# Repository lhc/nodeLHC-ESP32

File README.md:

## nodeLHC

# nodeLHC-ESP32

LIVE em formato Hands On Construindo o nova versão da placa de desenvolvimento nodeLHC ESP32, com o Pedro Minatel, utilizando a ferramenta Kicad, o módulo escolhido foi o ESP32 um microcontrolador de baixo custo da Espressif.

Em 2015 durante as oficinas de IoT no Hackerspace, criamos uma primeira versão do nodeLHC com o módulo ESP8266. Assim as pessoas aprenderam as diferentes etapas para construção de placa de circuitos impressos, também soldagem dos componentes da placa de desenvolvimento e programação para o módulo.

Descrições e detalhes:
Essa é uma primeira atividade que ao decorrer iremos construir novos projetos no formato aberto e colaborativo aproveitando a placa de desenvolvimento nodeLHC ESP32

- [KiCad](https://kicad.org/)
- [LHC KiCad Library](https://github.com/lhc/lhc_kicad_library)
- [Minatel KiCad Library](https://github.com/pedrominatel/minatel-kicad-libraries)
- [SparkFun KiCad Library](https://github.com/sparkfun/SparkFun-KiCad-Libraries)

# Checklist
- [x] LIVE 1 - Explicação geral e desenho
- [x] LIVE 2 - Revisão esquemático e desenho da PCB parcial
- [x] Lista de pessoas interessadas nos módulos
- [x] [20/11 às 20 horas : Feedback comunidade](https://discourse.lhc.net.br/t/parte-03-20-11-2020-coleta-de-feedback-do-nodelhc-esp32/225)
- [x] [LIVE 3 no dia 22 de janeiro de 2021 - Finalizar placa com KiCad](https://discourse.lhc.net.br/t/parte-05-finalizando-o-nodelhc-esp32-com-kicad/244)
- [x] Enviado o e-mail de confirmação aos interessados ao módulos ESP32
- [x] [Lista de interessados na compra coletiva](https://docs.google.com/forms/d/11yyAbOFoUoV5jsIAHc90laWFHk0OwfYHXRMlwPwyAws/edit)
- [x] Reunião online para novos revisores.
- [x] Validar artes na PCB (LHC/ Open Hardware)
- [x] [Videoconferência Revisão do nodeLHC: 25 Maio 2021 às 20 horas](meet.google.com/ngs-ypnc-mkd)

# Próximos passos
- [x] Convite Latinoware 2021
- [ ] Listar BOM / Orçamentos
- [ ] Produção da PCB
- [ ] LIVE de soldando o nodeLHC
- [ ] Distribuição para os participantes

# Checklist Review 01 nodeLHC

| Itens           | Check | Double Check  |
|---------------------|----------|----------|
| Alimentação 3V3| [Fechado](https://github.com/lhc/nodeLHC-ESP32/issues/2) | [Fechado](https://github.com/lhc/nodeLHC-ESP32/issues/9) |
| RX/TX| [Fechado](https://github.com/lhc/nodeLHC-ESP32/issues/3) | [Fechado](https://github.com/lhc/nodeLHC-ESP32/issues/10) |
| Reset e Boot| [Fechado](https://github.com/lhc/nodeLHC-ESP32/issues/4) | [Fechado](https://github.com/lhc/nodeLHC-ESP32/issues/11) |
| Conversor USB para UART| [Fechado](https://github.com/lhc/nodeLHC-ESP32/issues/5) | [Fechado](https://github.com/lhc/nodeLHC-ESP32/issues/12) |
| Conector Debug/JTAG| [Fechado](https://github.com/lhc/nodeLHC-ESP32/issues/6) | [Fechado](https://github.com/lhc/nodeLHC-ESP32/issues/13) |
| OLED| [Fechado](https://github.com/lhc/nodeLHC-ESP32/issues/7) | [Fechado](https://github.com/lhc/nodeLHC-ESP32/issues/14) |
| ESP32-WROMM pinout| [Fechado](https://github.com/lhc/nodeLHC-ESP32/issues/8) | [Fechado](https://github.com/lhc/nodeLHC-ESP32/issues/15) |

# Revisores
- Daniel
- Adrian
- Manassés
- Douglas

## Bill of Materials
| Component           | Quantity | Link                                             |
|---------------------|----------|--------------------------------------------------|
| ESP32-WROOM-   | 1        |                                                  |
|  |      |                                                  |

[Clique aqui](https://htmlpreview.github.io/?https://github.com/lhc/nodeLHC-ESP32/blob/master/projeto/bom/ibom.html) para ver a BOM interativa

Para gerar a BOM interativa, é necessário [instalar o plugin no KiCad](https://github.com/openscopeproject/InteractiveHtmlBom/wiki/Installation) e seguir as [orientações de uso](https://github.com/openscopeproject/InteractiveHtmlBom/wiki/Usage)

Para utilizar o plugin, no KiCad 6.x, após instalação concluída, utilize `PCB Editor > Tools > External Plugins > Generate Integractive HTML BOM`

# Vídeos gravados
- [Construindo o nodeLHC ESP32 com Kicad - Parte 01 #nodeLHC](https://youtu.be/l77AwA57H2A?t=1641)
- [Construindo o nodeLHC ESP32 com Kicad - Parte 02 #nodelhc](https://www.youtube.com/watch?v=WE6jsmoJX9M)
- [Construindo o nodeLHC ESP32 com Kicad - Parte 05](https://www.youtube.com/watch?v=1r1fcpELneA)

# Discourse
Dúvidas? sugestões publicar na issues ou direto no discourse do LHC
- [Parte 01 - 28/07/2020 LIVE - Hands On: Construindo o nodeLHC ESP32 com Kicad](https://discourse.lhc.net.br/t/28-07-2020-live-hands-on-construindo-o-nodelhc-esp32-com-kicad/148/2)
- [Parte 02 - Hands On: Construindo o nodeLHC ESP32 com Kicad](https://discourse.lhc.net.br/t/11-09-2020-live-hands-on-construindo-o-nodelhc-esp32-com-kicad-parte-02/160)
- [Parte 03 - Feedback comunidade](https://discourse.lhc.net.br/t/parte-03-20-11-2020-coleta-de-feedback-do-nodelhc-esp32/225)
- [Parte 04 - Melhorias para o nodeLHC ESP32](https://discourse.lhc.net.br/t/parte-04-melhorias-para-o-nodelhc-esp32/230/2)
- [Parte 05 - 22/01 às 20 horas: Hands On: Construindo o nodeLHC ESP32 com Kicad](https://discourse.lhc.net.br/t/parte-05-finalizando-o-nodelhc-esp32-com-kicad/244)

# Documentações em outras plataformas
- [Hackday.io](https://hackaday.io/project/177704-lhc-tijolo32-esp32-development-board)

# Log
- 19/08/2020 - Criado o evento, repositório, publicações nas redes sociais gerado link sobre a atividade.
- 02/09/2020 - Criado, divulgado o segundo evento, atualização de links no repositório.
- 06/10/2020 - Listagem das pessoas que responderam o discourse para receber o módulo ESP32
- 07/10/2020 - Chegaram os módulos.
- 17/11/2020 - Agendada conversa de feedback do projeto, divulgação da atividade.
- 16/01/2021 - Pedro fez update conforme o último encontro de feedback.
- 17/01/2021 - Atualizado no repositório, criado agenda de LIVE para o dia 22 de janeiro de 2021.
- 07/02/2021 - Enviado e-mail aos interessados aos módulos
             - Divulgação da compra coletiva de componentes para o nodeLHC
- 11/03/2021 - Atualização de revisão e update no projeto
- 16/03/2021 - Atualização de imagens e links de gravações
- 30/05/2021 - Feedback do Daniel registrado e atualização no README.md

### Referências
- [ESP32 Datasheet](https://www.espressif.com/sites/default/files/documentation/esp32_datasheet_en.pdf)
- [ESP32-WROOM Datasheet](https://www.espressif.com/sites/default/files/documentation/esp32-wroom-32d_esp32-wroom-32u_datasheet_en.pdf)
- [ESP32 Design Guidelines](https://www.espressif.com/sites/default/files/documentation/esp32_hardware_design_guidelines_en.pdf)
- [CH340G](https://cdn.sparkfun.com/datasheets/Dev/Arduino/Other/CH340DS1.PDF)
- [Open Source Hardware Association](https://www.oshwa.org/definition/)

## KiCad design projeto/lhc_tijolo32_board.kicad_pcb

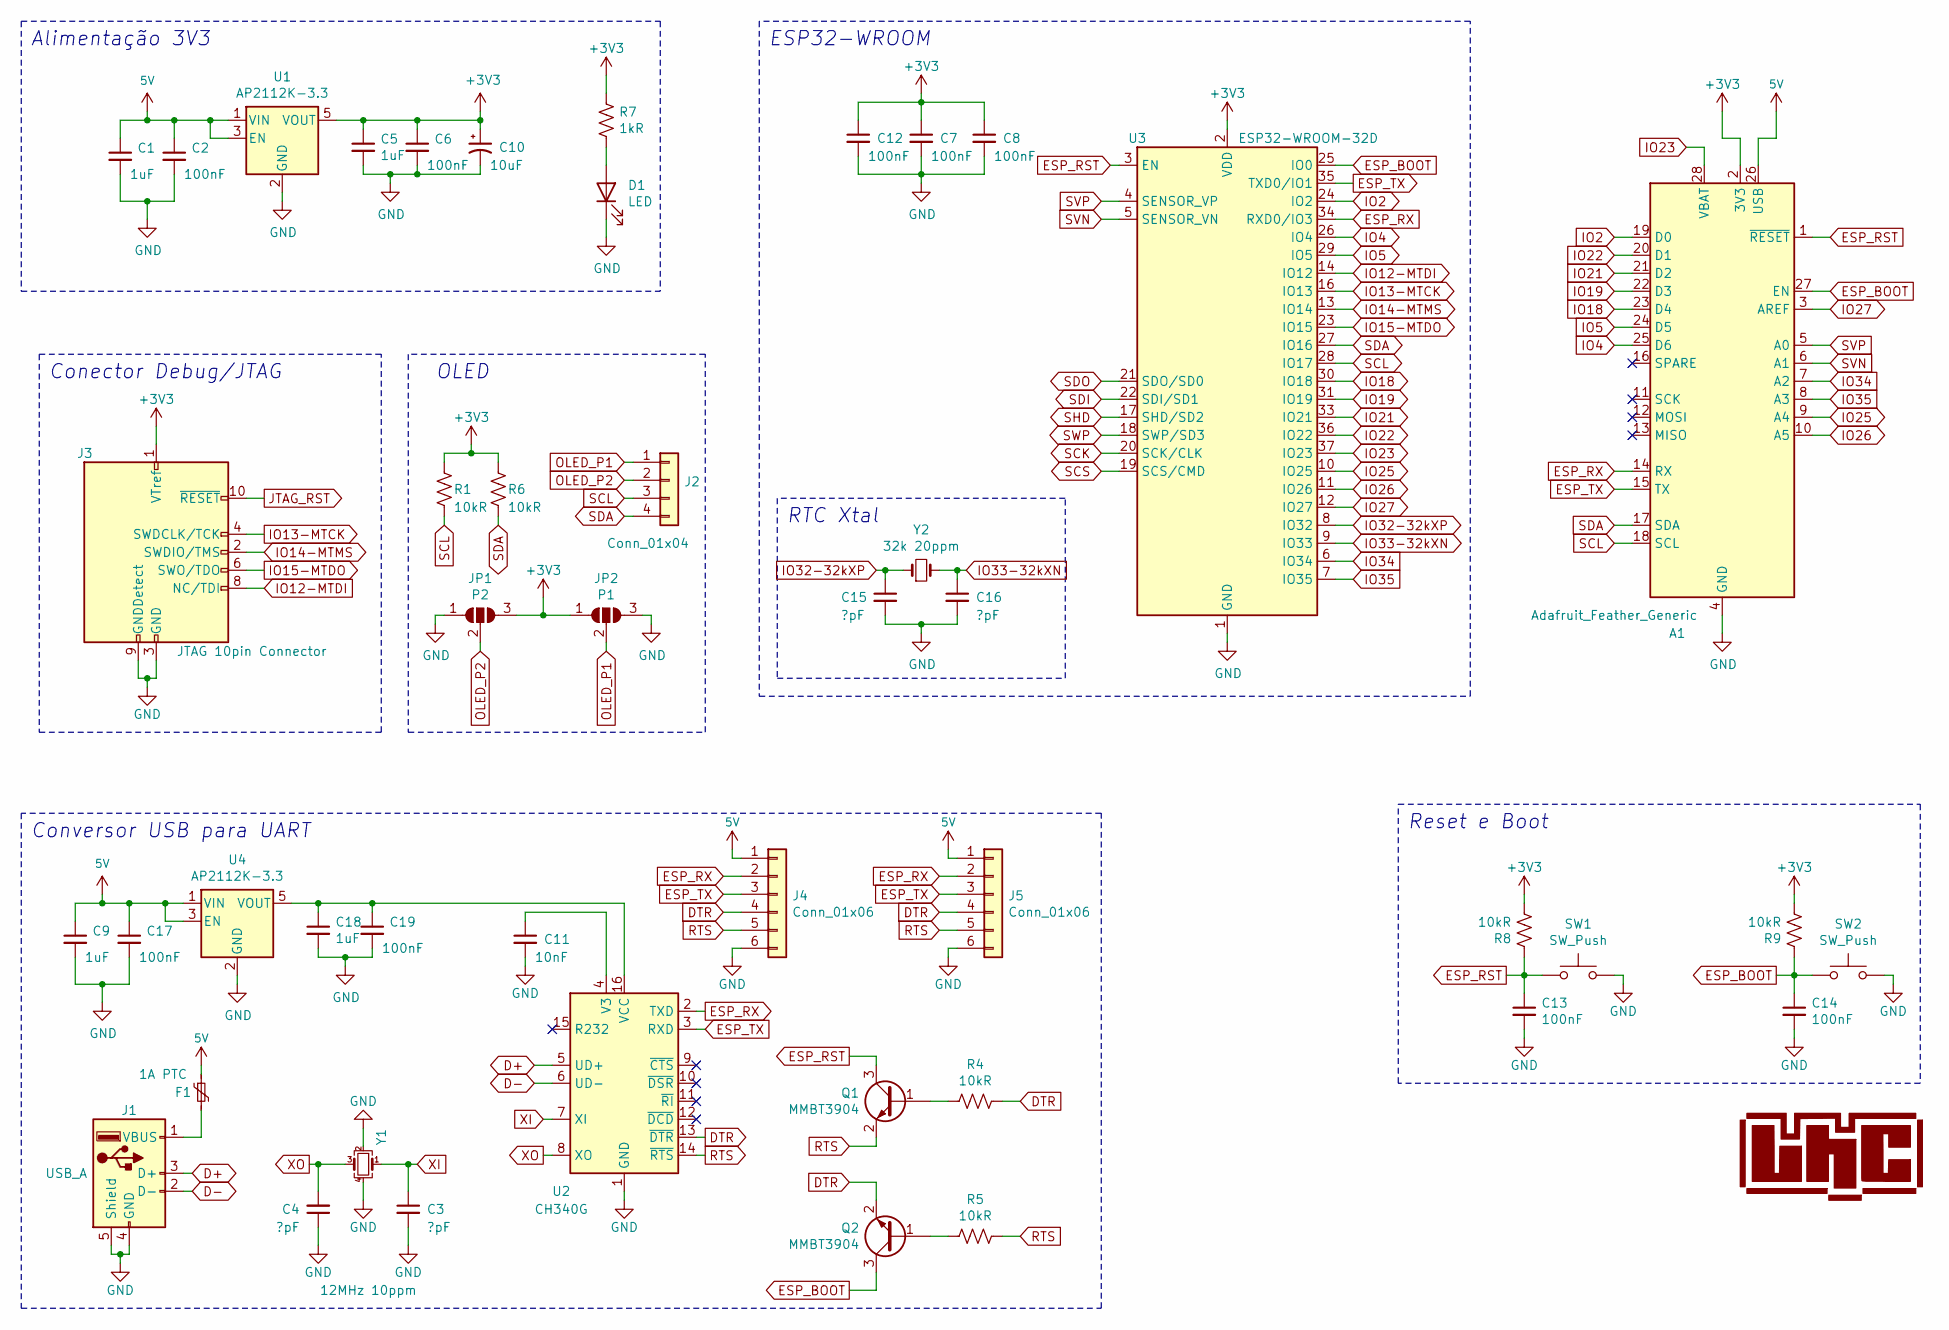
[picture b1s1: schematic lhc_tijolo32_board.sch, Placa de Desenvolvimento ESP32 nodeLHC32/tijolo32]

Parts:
A1: Adafruit_Feather_Generic; Adafruit_Feather
C1, C5, C9, C18: 1uF; C_0603_1608Metric
C2, C6, C7, C8, C12, C13, C14, C17, C19: 100nF; C_0603_1608Metric
C3, C4, C15, C16: ?pF; C_0603_1608Metric
C10: 10uF; CP_EIA-3216-12_Kemet-S; LCSC C7171
C11: 10nF; C_0603_1608Metric
D1: LED; LED_0805_2012Metric
F1: 1A PTC; R_1210_3225Metric
J1: USB_A; USB_A_CNCTech_1001-011-01101_Horizontal
J2: Conn_01x04; PinSocket_1x04_P2.54mm_Vertical
J3: JTAG 10pin Connector; PinHeader_2x05_P1.27mm_Vertical_SMD
J4, J5: Conn_01x06; PinSocket_1x06_P2.54mm_Vertical
JP1: P2; SolderJumper-3_P1.3mm_Open_Pad1.0x1.5mm_NumberLabels
JP2: P1; SolderJumper-3_P1.3mm_Open_Pad1.0x1.5mm_NumberLabels
Q1, Q2: MMBT3904; SOT-23
R1, R4, R5, R6, R8, R9: 10kR; R_0603_1608Metric
R7: 1kR; R_0603_1608Metric
SW1, SW2: SW_Push; TACTILE_SWITCH_SMD_6.0X3.5MM
U1, U4: AP2112K-3.3; SOT-23-5
U2: CH340G; SOIC-16_3.9x9.9mm_P1.27mm; MPN C14267
U3: ESP32-WROOM-32D; ESP32-WROOM-32
Y1: 12MHz 10ppm; Crystal_SMD_EuroQuartz_MT-4Pin_3.2x2.5mm
Y2: 32k 20ppm; Crystal_SMD_3215-2Pin_3.2x1.5mm

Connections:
5V: A1.26 (USB), C1.1, C2.1, C9.1, C17.1, F1.1, J4.1, J5.1, U1.1 (VIN), U1.3 (EN), U4.1 (VIN), U4.3 (EN)
+3V3: A1.2 (3V3), C5.1, C6.1, C7.1, C8.1, C10.1, C12.1, J3.1 (VTref), JP1.3 (B), JP2.1 (A), R1.1, R6.1, R7.1, R8.2, R9.2, U1.5 (VOUT), U3.2 (VDD)
D+: J1.3 (D+), U2.5 (UD+)
D-: J1.2 (D-), U2.6 (UD-)
DTR: J4.4, J5.4, Q2.2 (E), R4.1, U2.13 (~DTR)
ESP_BOOT: A1.27 (EN), C14.1, Q2.3 (C), R9.1, SW2.1, U3.25 (IO0)
ESP_RST: A1.1 (~RESET), C13.1, Q1.3 (C), R8.1, SW1.1, U3.3 (EN)
ESP_RX: A1.14 (RX), J4.2, J5.2, U2.2 (TXD), U3.34 (RXD0/IO3)
ESP_TX: A1.15 (TX), J4.3, J5.3, U2.3 (RXD), U3.35 (TXD0/IO1)
GND: A1.4 (GND), C1.2, C2.2, C3.2, C4.1, C5.2, C6.2, C7.2, C8.2, C9.2, C10.2, C11.2, C12.2, C13.2, C14.2, C15.2, C16.2, C17.2, C18.2, C19.2, D1.1 (K), J1.4 (GND), J1.5 (Shield), J3.3 (GND), J3.5 (GND), J3.9 (GNDDetect), J4.6, J5.6, JP1.1 (A), JP2.3 (B), SW1.2, SW2.2, U1.2 (GND), U2.1 (GND), U3.1 (GND), U3.15 (GND), U3.38 (GND), U3.39 (GND), U4.2 (GND), Y1.2, Y1.4
IO2: A1.19 (D0), U3.24 (IO2)
IO4: A1.25 (D6), U3.26 (IO4)
IO5: A1.24 (D5), U3.29 (IO5)
IO12-MTDI: J3.8 (NC/TDI), U3.14 (IO12)
IO13-MTCK: J3.4 (SWDCLK/TCK), U3.16 (IO13)
IO14-MTMS: J3.2 (SWDIO/TMS), U3.13 (IO14)
IO15-MTDO: J3.6 (SWO/TDO), U3.23 (IO15)
IO18: A1.23 (D4), U3.30 (IO18)
IO19: A1.22 (D3), U3.31 (IO19)
IO21: A1.21 (D2), U3.33 (IO21)
IO22: A1.20 (D1), U3.36 (IO22)
IO23: A1.28 (VBAT), U3.37 (IO23)
IO25: A1.9 (A4), U3.10 (IO25)
IO26: A1.10 (A5), U3.11 (IO26)
IO27: A1.3 (AREF), U3.12 (IO27)
IO32-32kXP: C15.1, U3.8 (IO32), Y2.1
IO33-32kXN: C16.1, U3.9 (IO33), Y2.2
IO34: A1.7 (A2), U3.6 (IO34)
IO35: A1.8 (A3), U3.7 (IO35)
JTAG_RST: J3.10 (~RESET~)
unnamed: C11.1, U2.4 (V3)
unnamed: C18.1, C19.1, U2.16 (VCC), U4.5 (VOUT)
unnamed: D1.2 (A), R7.2
unnamed: F1.2, J1.1 (VBUS)
unnamed: Q1.1 (B), R4.2
unnamed: Q2.1 (B), R5.2
OLED_P1: J2.1, JP2.2 (C)
OLED_P2: J2.2, JP1.2 (C)
RTS: J4.5, J5.5, Q1.2 (E), R5.1, U2.14 (~RTS)
SCK: U3.20 (SCK/CLK)
SCL: A1.18 (SCL), J2.3, R1.2, U3.28 (IO17)
SCS: U3.19 (SCS/CMD)
SDA: A1.17 (SDA), J2.4, R6.2, U3.27 (IO16)
SDI: U3.22 (SDI/SD1)
SDO: U3.21 (SDO/SD0)
SHD: U3.17 (SHD/SD2)
SVN: A1.6 (A1), U3.5 (SENSOR_VN)
SVP: A1.5 (A0), U3.4 (SENSOR_VP)
SWP: U3.18 (SWP/SD3)
XI: C3.1, U2.7 (XI), Y1.1
XO: C4.2, U2.8 (XO), Y1.3

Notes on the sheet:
Alimentação 3V3
Conversor USB para UART
Conector Debug/JTAG
Reset e Boot
OLED
ESP32-WROOM
RTC Xtal

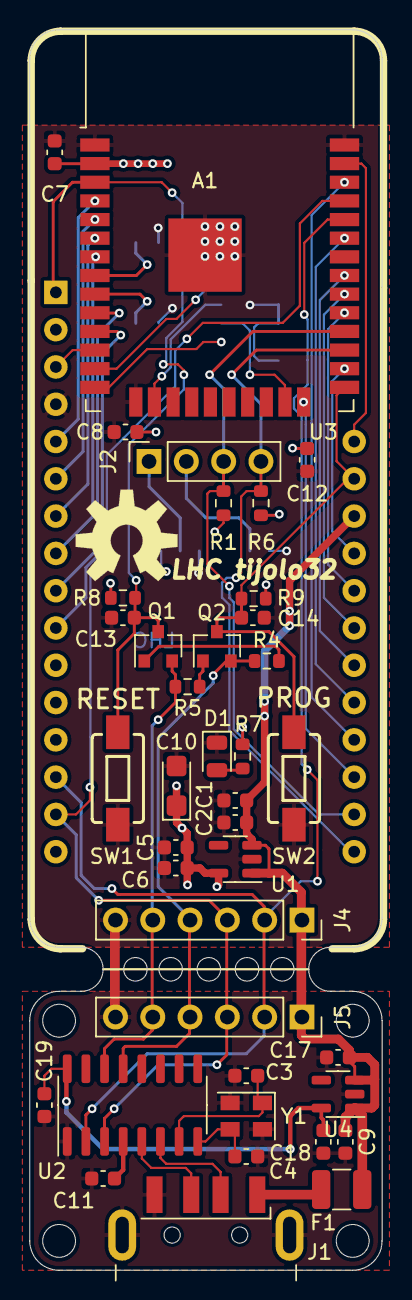
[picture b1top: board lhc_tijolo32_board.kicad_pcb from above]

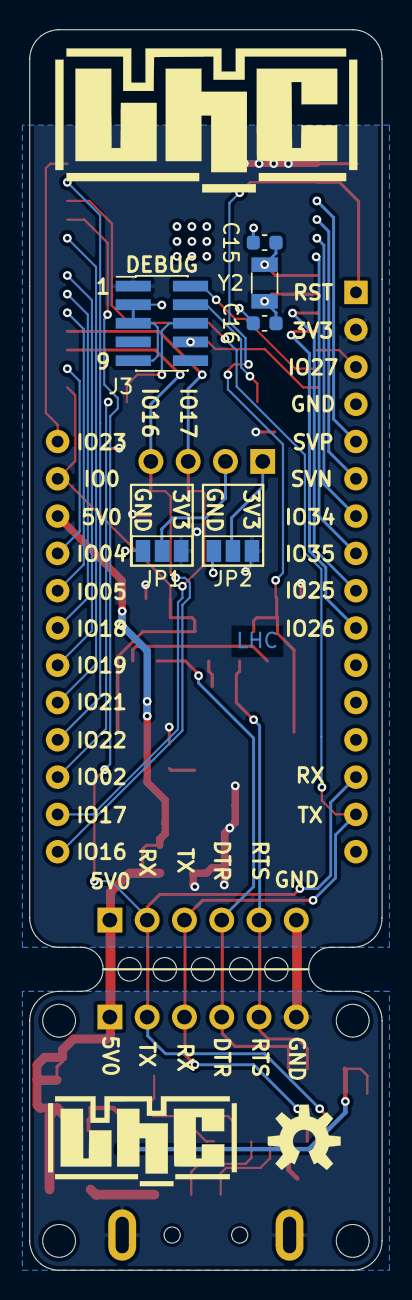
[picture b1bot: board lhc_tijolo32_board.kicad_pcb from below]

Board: 2 copper layers, 24.0 x 84.5 mm, 46 parts (6 on the bottom side), 44 nets.

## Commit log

2021-01-16 Removed old files *project-name*
2021-01-16 Changed from Sparkfun to Adafruit Feather layout
2021-01-16 Layout updated and added new 3d images
2021-01-20 Layout updated
2021-01-22 Layout improved
2021-01-23 Layout LIVE
2021-02-13 Updated silk on both sides
2021-02-13 Updated 3D image
2021-03-21 add interactive BOM
2021-06-16 Branch for ESP32-S2
2021-06-17 Added README
2021-07-04 Updated on some labels, footprints and symbols
2021-07-18 Componentes 3D adicionados
2021-07-18 GERBER atualizado
2021-07-18 #d dos botoes
2021-11-08 Update README.md
    https://forum.kicad.info/t/warning-avoid-all-links-to-kicad-pcb-org-use-kicad-org/31521
2022-01-09 update interactive BOM
2022-01-09 update README with instructions for interactive BOM
